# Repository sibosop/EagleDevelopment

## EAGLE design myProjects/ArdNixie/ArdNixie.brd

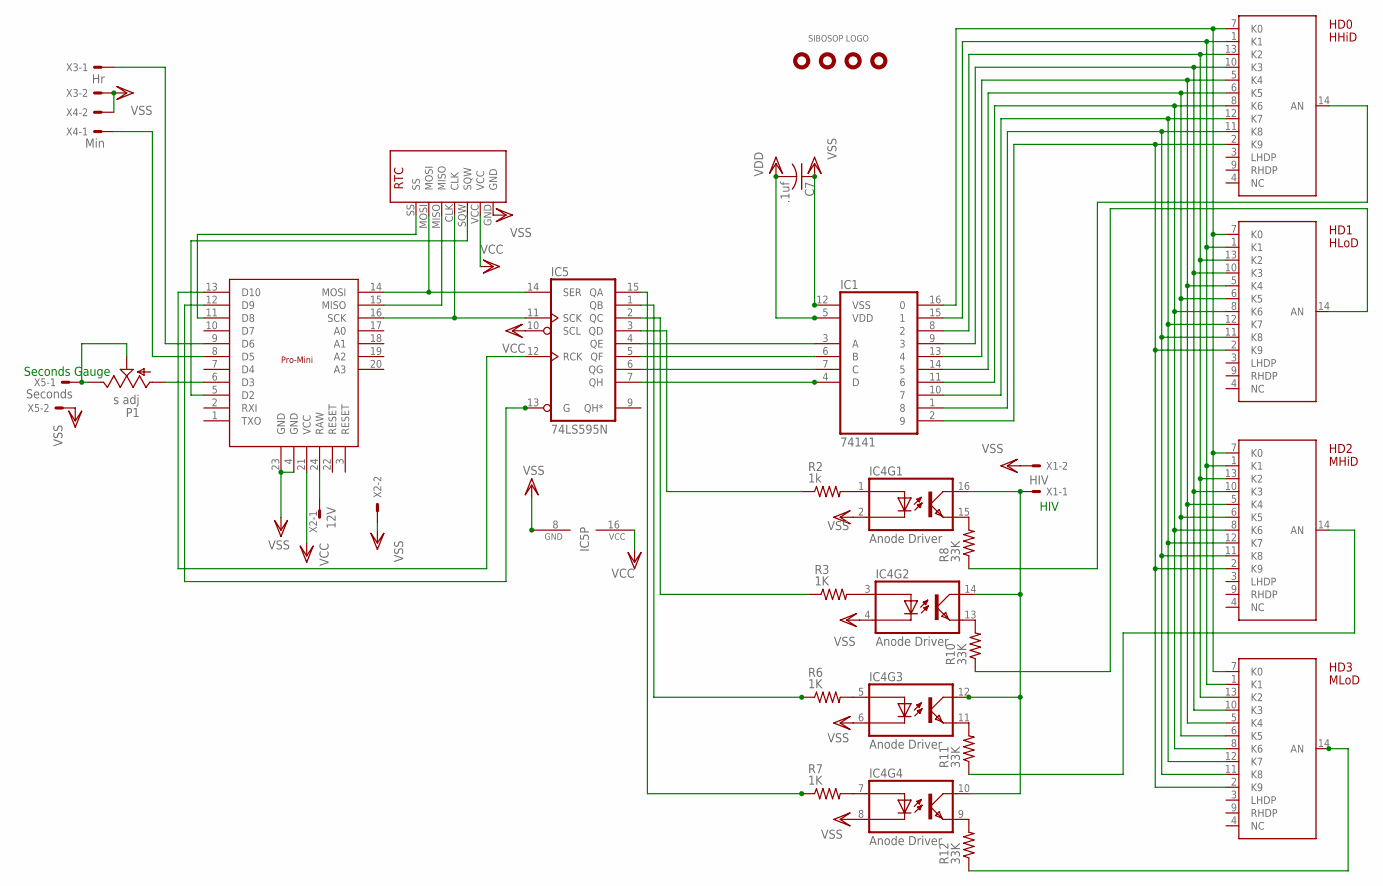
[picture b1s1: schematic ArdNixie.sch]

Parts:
C7: .1uf; C025-024X044
HD0: HHiD; DIL14
HD1: HLoD; DIL14
HD2: MHiD; DIL14
HD3: MLoD; DIL14
IC1: 74141; DIP16
IC2: PRO-MINI; DIL24-6-EXT
IC3: SPARKRTC
IC4: Anode Driver; DIP16
IC5: 74LS595N; DIL16
P1: s adj; RJ6S
R2: 1k; 0204V
R3, R6, R7: 1K; 0204V
R8, R10, R11, R12: 33K; 0204V
U$1, U$2, U$5, U$7: HOLE-125
U$3: LOGO
X1: HIV; 22-23-2021
X2: 12V; 22-23-2021
X3: Hr; 22-23-2021
X4: Min; 22-23-2021
X5: Seconds; 22-23-2021

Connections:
unnamed: IC5.15 (QA), R7.1
unnamed: IC5.1 (QB), R6.1
unnamed: IC5.2 (QC), R3.1
unnamed: IC5.3 (QD), R2.1
unnamed: IC1.3 (A), IC5.4 (QE)
unnamed: IC1.6 (B), IC5.5 (QF)
unnamed: HD0.7 (K0), HD1.7 (K0), HD2.7 (K0), HD3.7 (K0), IC1.16 (0)
unnamed: HD0.1 (K1), HD1.1 (K1), HD2.1 (K1), HD3.1 (K1), IC1.15 (1)
unnamed: HD0.13 (K2), HD1.13 (K2), HD2.13 (K2), HD3.13 (K2), IC1.8 (2)
unnamed: HD0.10 (K3), HD1.10 (K3), HD2.10 (K3), HD3.10 (K3), IC1.9 (3)
unnamed: HD0.5 (K4), HD1.5 (K4), HD2.5 (K4), HD3.5 (K4), IC1.13 (4)
unnamed: P1.E, P1.S, X5.1
unnamed: HD0.8 (K6), HD1.8 (K6), HD2.8 (K6), HD3.8 (K6), IC1.11 (6)
unnamed: HD0.12 (K7), HD1.12 (K7), HD2.12 (K7), HD3.12 (K7), IC1.10 (7)
unnamed: HD0.11 (K8), HD1.11 (K8), HD2.11 (K8), HD3.11 (K8), IC1.1 (8)
unnamed: HD0.2 (K9), HD1.2 (K9), HD2.2 (K9), HD3.2 (K9), IC1.2 (9)
unnamed: IC1.7 (C), IC5.6 (QG)
unnamed: IC1.4 (D), IC5.7 (QH)
unnamed: IC2.24 (RAW), X2.1
unnamed: IC2.11 (D8), IC3.SS
unnamed: HD0.6 (K5), HD1.6 (K5), HD2.6 (K5), HD3.6 (K5), IC1.14 (5)
unnamed: IC2.16 (SCK), IC3.CLK, IC5.11 (SCK)
unnamed: IC2.15 (MISO), IC3.MISO
unnamed: IC4.1 (AN), R2.2
unnamed: IC4.5 (AN), R6.2
unnamed: IC4.7 (AN), R7.2
unnamed: IC2.14 (MOSI), IC3.MOSI, IC5.14 (SER)
unnamed: IC2.5 (D2), IC3.SQW
unnamed: IC2.12 (D9), IC5.13 (G)
unnamed: IC2.13 (D10), IC5.12 (RCK)
unnamed: IC2.6 (D3), P1.A
unnamed: IC4.3 (AN), R3.2
unnamed: IC2.8 (D5), X4.1
unnamed: IC4.15 (EM), R8.2
unnamed: IC4.13 (EM), R10.2
unnamed: IC4.11 (EM), R11.2
unnamed: IC4.9 (EM), R12.2
unnamed: HD0.14 (AN), R8.1
unnamed: HD1.14 (AN), R10.1
unnamed: HD2.14 (AN), R11.1
unnamed: HD3.14 (AN), R12.1
unnamed: IC2.9 (D6), X3.1
unnamed: IC4.10 (CO), IC4.12 (CO), IC4.14 (CO), IC4.16 (CO), X1.1
VDD: C7.2, IC1.5 (VDD), IC2.21 (VCC), IC3.VCC, IC5.10 (SCL), IC5.16 (VCC)
VSS: C7.1, IC1.12 (VSS), IC2.4 (GND), IC2.23 (GND), IC3.GND, IC4.2 (CA), IC4.4 (CA), IC4.6 (CA), IC4.8 (CA), IC5.8 (GND), X1.2, X2.2, X3.2, X4.2, X5.2

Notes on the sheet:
Seconds Gauge
HIV

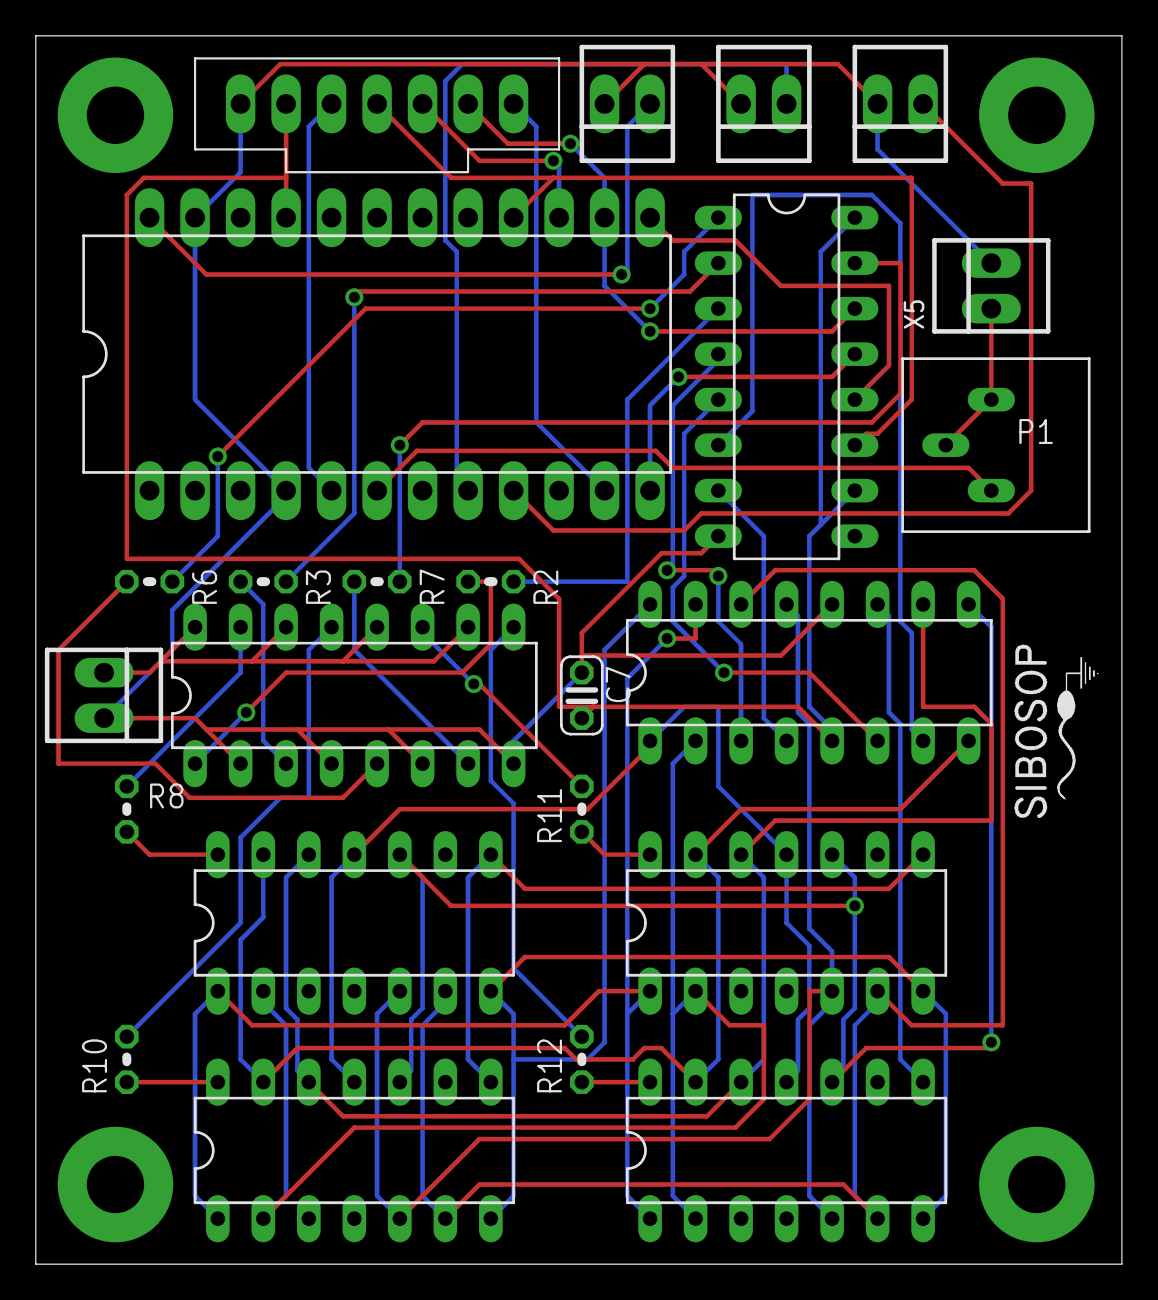
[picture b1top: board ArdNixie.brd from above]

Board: 2 copper layers, 60.6 x 68.6 mm, 29 parts (0 on the bottom side), 45 nets.

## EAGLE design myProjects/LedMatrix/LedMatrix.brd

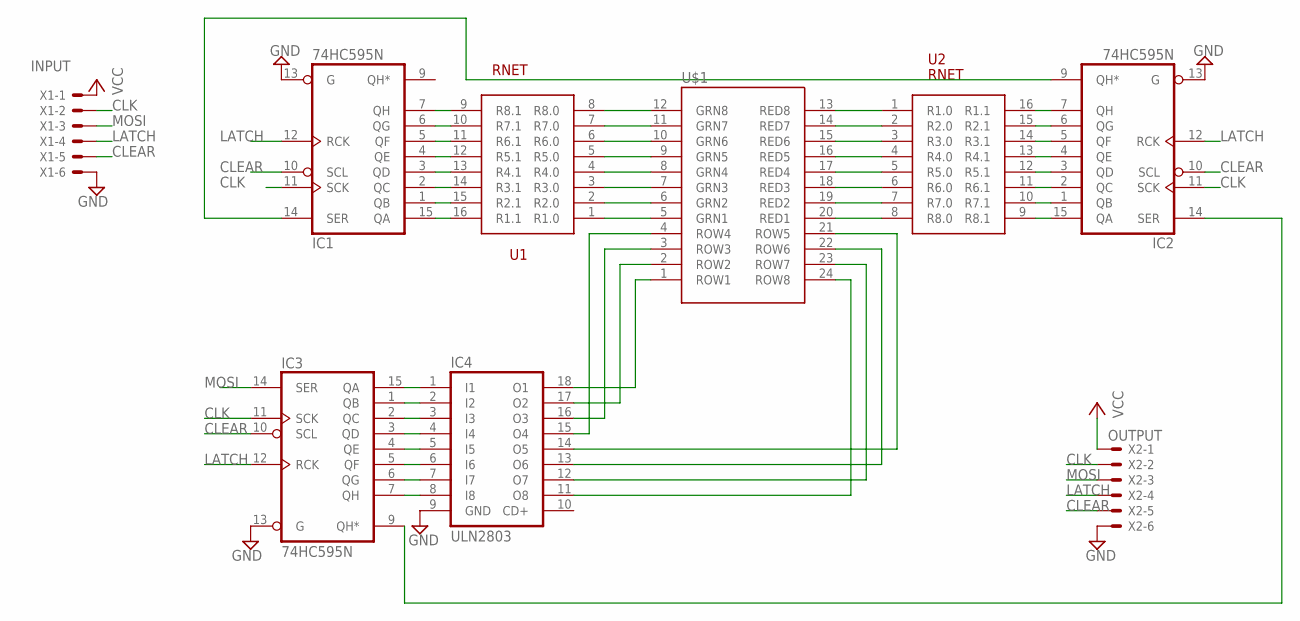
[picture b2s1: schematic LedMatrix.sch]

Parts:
IC1, IC2, IC3: 74HC595N; DIL16
IC4: ULN2803; DIL18
U1, U2: RNET; DIP16
U$1: WLG-M2088A/8EG
X1: INPUT; 22-23-2061
X2: OUTPUT; 22-23-2061

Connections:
CLEAR: IC1.10 (SCL), IC2.10 (SCL), IC3.10 (SCL), X1.5, X2.5
CLK: IC1.11 (SCK), IC2.11 (SCK), IC3.11 (SCK), X1.2, X2.2
GND: IC1.8 (GND), IC1.13 (G), IC2.8 (GND), IC2.13 (G), IC3.8 (GND), IC3.13 (G), IC4.9 (GND), X1.6, X2.6
LATCH: IC1.12 (RCK), IC2.12 (RCK), IC3.12 (RCK), X1.4, X2.4
MOSI: IC3.14 (SER), X1.3, X2.3
unnamed: IC1.1 (QB), U1.15 (R2.1)
unnamed: IC1.2 (QC), U1.14 (R3.1)
unnamed: IC1.3 (QD), U1.13 (R4.1)
unnamed: IC1.4 (QE), U1.12 (R5.1)
unnamed: IC1.5 (QF), U1.11 (R6.1)
unnamed: IC1.6 (QG), U1.10 (R7.1)
unnamed: IC1.7 (QH), U1.9 (R8.1)
unnamed: IC1.15 (QA), U1.16 (R1.1)
unnamed: U1.1 (R1.0), U$1.5 (GRN1)
unnamed: U1.2 (R2.0), U$1.6 (GRN2)
unnamed: U1.3 (R3.0), U$1.7 (GRN3)
unnamed: U1.4 (R4.0), U$1.8 (GRN4)
unnamed: U1.5 (R5.0), U$1.9 (GRN5)
unnamed: U1.6 (R6.0), U$1.10 (GRN6)
unnamed: U1.7 (R7.0), U$1.11 (GRN7)
unnamed: U1.8 (R8.0), U$1.12 (GRN8)
unnamed: U2.1 (R1.0), U$1.13 (RED8)
unnamed: U2.2 (R2.0), U$1.14 (RED7)
unnamed: U2.3 (R3.0), U$1.15 (RED6)
unnamed: U2.4 (R4.0), U$1.16 (RED5)
unnamed: U2.5 (R5.0), U$1.17 (RED4)
unnamed: U2.6 (R6.0), U$1.18 (RED3)
unnamed: U2.7 (R7.0), U$1.19 (RED2)
unnamed: U2.8 (R8.0), U$1.20 (RED1)
unnamed: IC2.1 (QB), U2.10 (R7.1)
unnamed: IC2.2 (QC), U2.11 (R6.1)
unnamed: IC2.3 (QD), U2.12 (R5.1)
unnamed: IC2.4 (QE), U2.13 (R4.1)
unnamed: IC2.5 (QF), U2.14 (R3.1)
unnamed: IC2.6 (QG), U2.15 (R2.1)
unnamed: IC2.7 (QH), U2.16 (R1.1)
unnamed: IC2.15 (QA), U2.9 (R8.1)
unnamed: IC3.1 (QB), IC4.2 (I2)
unnamed: IC3.2 (QC), IC4.3 (I3)
unnamed: IC3.3 (QD), IC4.4 (I4)
unnamed: IC3.4 (QE), IC4.5 (I5)
unnamed: IC3.5 (QF), IC4.6 (I6)
unnamed: IC3.6 (QG), IC4.7 (I7)
unnamed: IC3.7 (QH), IC4.8 (I8)
unnamed: IC3.15 (QA), IC4.1 (I1)
unnamed: IC4.18 (O1), U$1.1 (ROW1)
unnamed: IC4.17 (O2), U$1.2 (ROW2)
unnamed: IC4.16 (O3), U$1.3 (ROW3)
unnamed: IC4.15 (O4), U$1.4 (ROW4)
unnamed: IC4.14 (O5), U$1.21 (ROW5)
unnamed: IC4.13 (O6), U$1.22 (ROW6)
unnamed: IC4.12 (O7), U$1.23 (ROW7)
unnamed: IC4.11 (O8), U$1.24 (ROW8)
unnamed: IC2.14 (SER), IC3.9 (QH*)
unnamed: IC1.14 (SER), IC2.9 (QH*)
VCC: IC1.16 (VCC), IC2.16 (VCC), IC3.16 (VCC), X1.1, X2.1

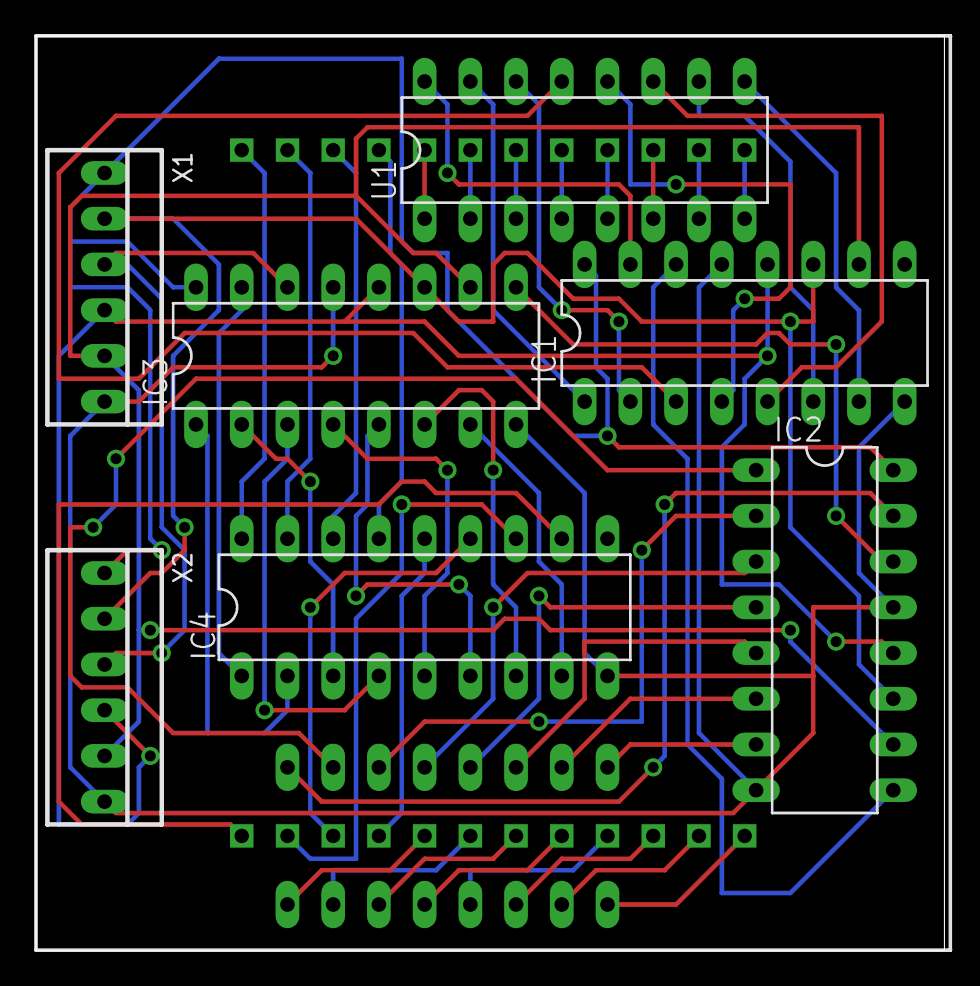
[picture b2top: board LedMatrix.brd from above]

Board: 2 copper layers, 50.5 x 50.8 mm, 9 parts (1 on the bottom side), 56 nets.

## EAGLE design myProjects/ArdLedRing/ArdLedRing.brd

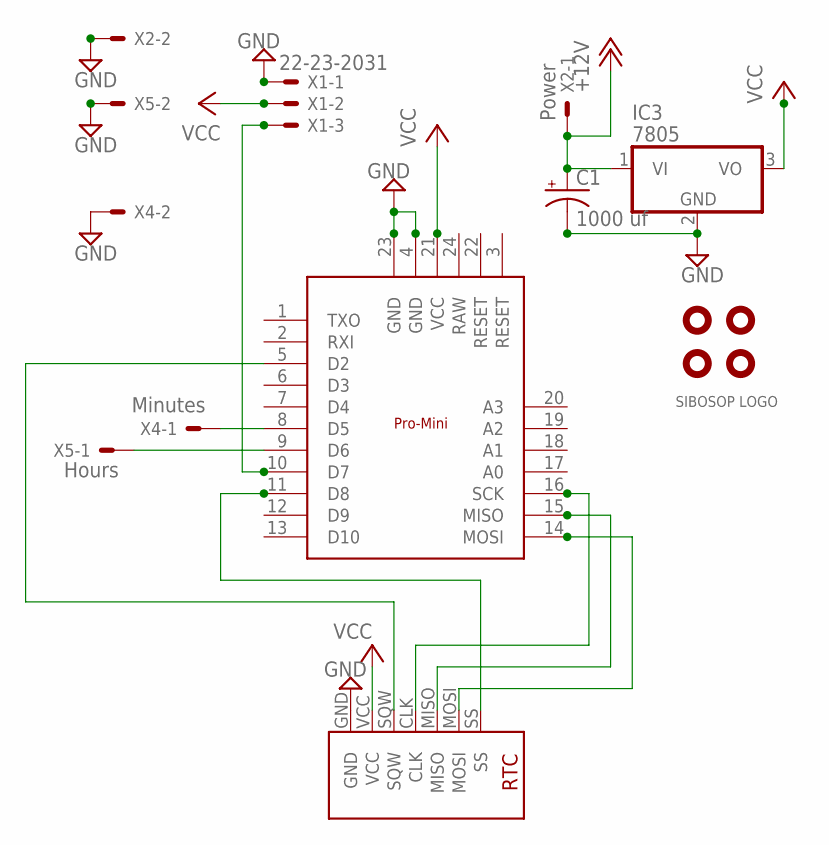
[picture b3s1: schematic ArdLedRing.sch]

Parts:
C1: 1000 uf; E3,5-10
IC1: PRO-MINI; DIL24-6-EXT
IC2: SPARKRTC
IC3: 7805; TO220V
U$1: LOGO
U$2, U$3, U$4, U$5: HOLE-125
X1: 22-23-2031
X2: Power; 22-23-2021
X4: Minutes; 22-23-2021
X5: Hours; 22-23-2021

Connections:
+12V: C1.+, IC3.1 (VI), X2.1
GND: C1.-, IC1.4 (GND), IC1.23 (GND), IC2.GND, IC3.2 (GND), X1.1, X2.2, X4.2, X5.2
unnamed: IC1.8 (D5), X4.1
unnamed: IC1.9 (D6), X5.1
unnamed: IC1.5 (D2), IC2.SQW
unnamed: IC1.16 (SCK), IC2.CLK
unnamed: IC1.15 (MISO), IC2.MISO
unnamed: IC1.14 (MOSI), IC2.MOSI
unnamed: IC1.11 (D8), IC2.SS
unnamed: IC1.10 (D7), X1.3
RAW: IC1.24 (RAW)
VCC: IC1.21 (VCC), IC2.VCC, IC3.3 (VO), X1.2

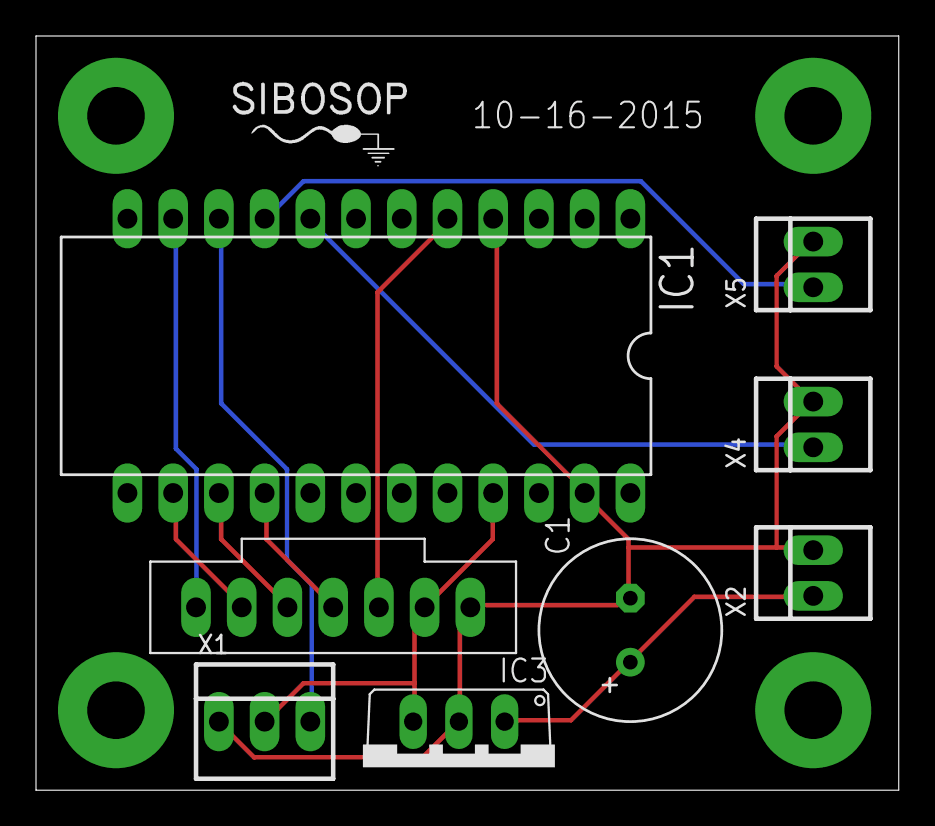
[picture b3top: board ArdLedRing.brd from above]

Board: 2 copper layers, 47.9 x 41.9 mm, 13 parts (0 on the bottom side), 11 nets.

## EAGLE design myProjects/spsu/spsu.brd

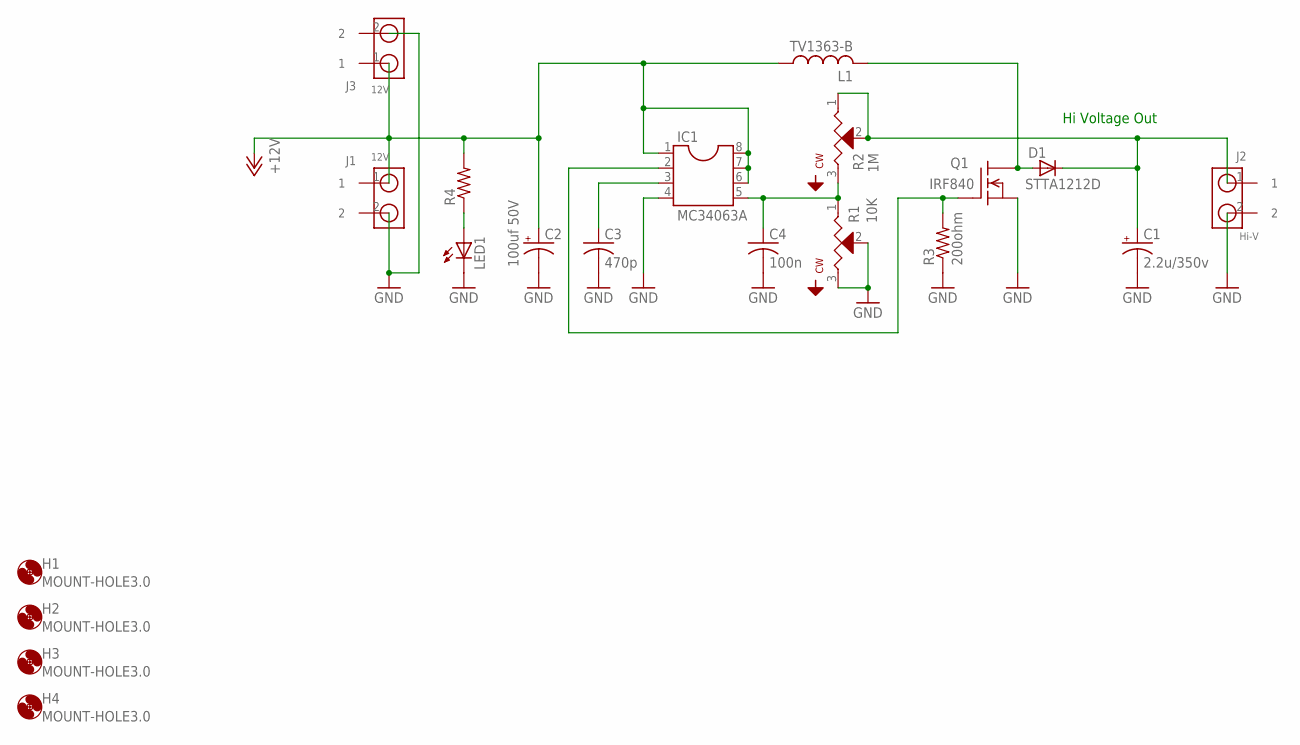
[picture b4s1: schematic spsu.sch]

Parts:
C1: 2.2u/350v; E5-8,5
C2: 100uf 50V; E5-8,5
C3: 470p; C025-040X050
C4: 100n; C025-040X050
D1: STTA1212D; TO220ACS
H1, H2, H3, H4: MOUNT-HOLE3.0; 3,0
IC1: MC34063A; DIL08
J1, J3: 12V; MOLEX-001-2PIN
J2: Hi-V; MOLEX-001-2PIN
L1: TV1363-B; RADIAL-VMOUNT-8-5MM
LED1: LED3MM
Q1: IRF840; TO220V
R1: 10K; .25IN-TOP-TRIMPOT
R2: 1M; .25IN-TOP-TRIMPOT
R3: 200ohm; 0204/5
R4: R-US_0204/5; 0204/5

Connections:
+12V: C2.+, IC1.1, IC1.6, IC1.7, IC1.8, J1.1, J3.1, L1.1, R4.2
GND: C1.-, C2.-, C3.2, C4.2, IC1.4, J1.2, J2.2, J3.2, LED1.K (C), Q1.3 (S), R1.2, R1.3, R3.1
HIVOLTAGEOUT: C1.+, D1.C, J2.1, R2.1, R2.2
unnamed: LED1.A, R4.1
unnamed: D1.A, L1.2, Q1.2 (D)
unnamed: C4.1, IC1.5, R1.1, R2.3
unnamed: C3.1, IC1.3
unnamed: IC1.2, Q1.1 (G), R3.2

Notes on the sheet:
Hi Voltage Out

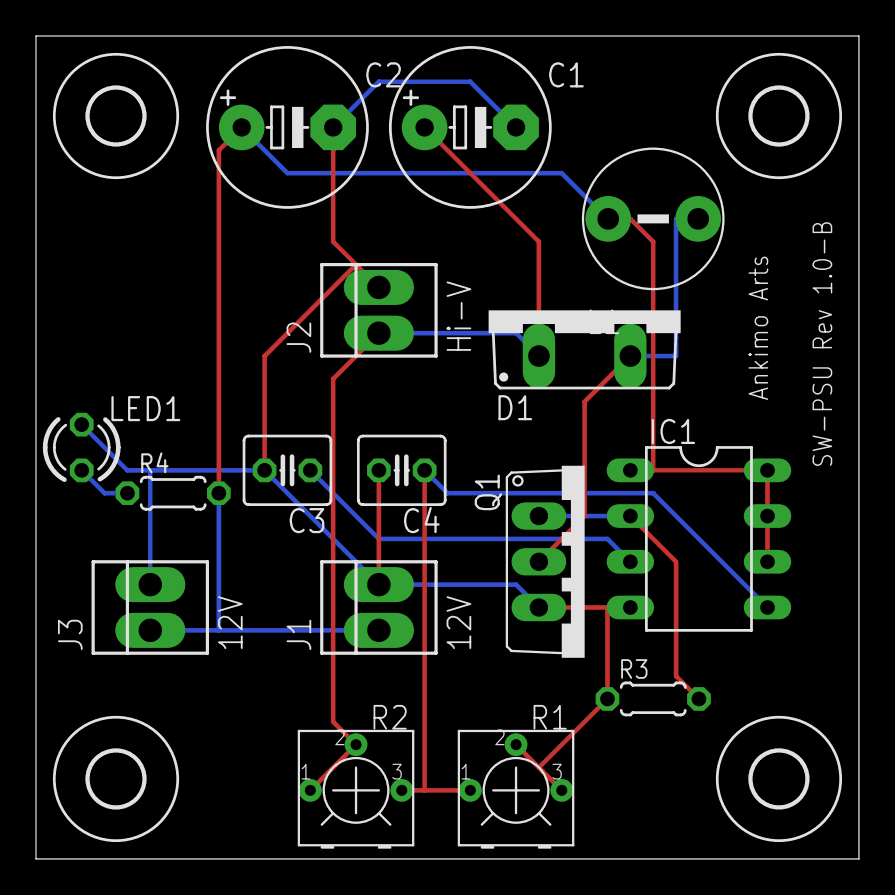
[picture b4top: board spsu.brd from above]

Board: 2 copper layers, 45.7 x 45.7 mm, 20 parts (0 on the bottom side), 8 nets.

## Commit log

2007-11-04 new_pjt
2007-11-04 initial revision
2007-11-16 added Pcb Express projects
2007-11-16 added basic pic and lcdboard
2007-11-30 added con molex
2010-12-23 checkpoint added missing schematics
2011-11-01 general backup for laptop switch
2011-12-05 testing new svn
2012-04-17 lodi disaster recovery
2012-04-17 recovering from lodi disaster 4
2012-06-18 added Gerber
2012-06-18 removed power plugs and replaces with molex added Gerber files
2015-10-11 added ArdLedRing project
2015-10-11 added svn changes I missed on convert
2015-10-19 finished ArdLedRing design
2015-11-02 new project for LedMatrix
2015-11-04 completed board for led matrix
2015-11-04 fixed some labelling
2015-11-21 added rtNixie
2015-12-28 added ArdNixie
2015-12-28 finished premil board layout for ardnixie
2015-12-30 finished first board design for ArdNixie
2015-12-30 provided some room for nixie headers
2015-12-30 added DS_Store to gitignore
